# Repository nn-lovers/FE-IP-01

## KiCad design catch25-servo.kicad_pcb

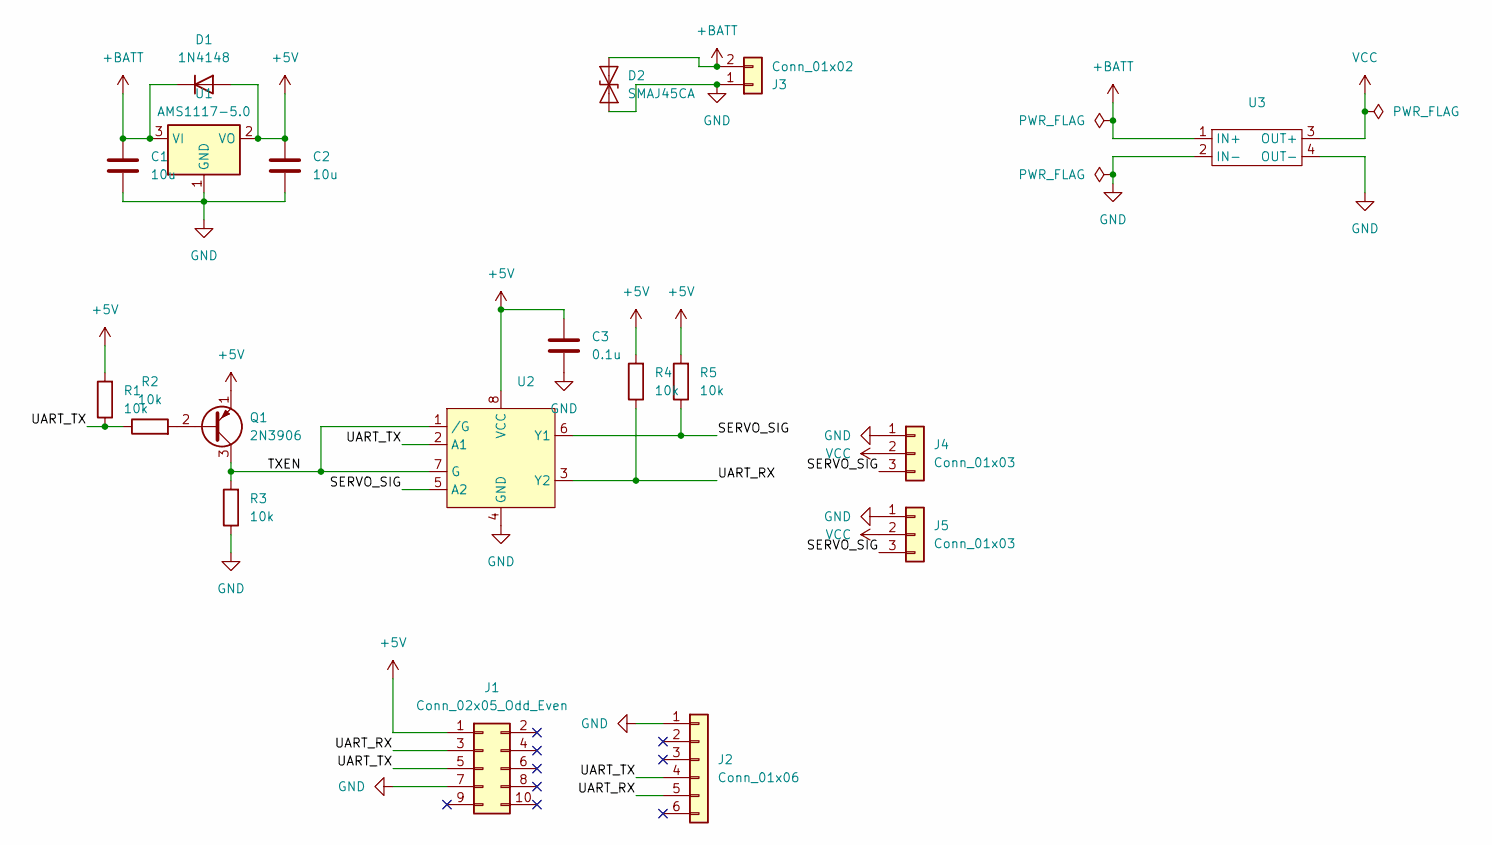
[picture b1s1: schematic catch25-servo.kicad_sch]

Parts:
C1, C2: 10u; C_0603_1608Metric_Pad1.08x0.95mm_HandSolder
C3: 0.1u; C_0603_1608Metric_Pad1.08x0.95mm_HandSolder
D1: 1N4148; D_DO-35_SOD27_P7.62mm_Horizontal
D2: SMAJ45CA; D_SMA_Handsoldering
J1: Conn_02x05_Odd_Even; PinSocket_2x05_P2.54mm_Horizontal
J2: Conn_01x06; PinSocket_1x06_P2.54mm_Vertical
J3: Conn_01x02; AMASS_XT30PW-M_1x02_P2.50mm_Horizontal
J4, J5: Conn_01x03; Molex_SPOX_5268-03A_1x03_P2.50mm_Horizontal
Q1: 2N3906; SuperSOT-3
R1, R2, R3, R4, R5: 10k; R_0603_1608Metric_Pad0.98x0.95mm_HandSolder
U1: AMS1117-5.0; SOT-223-3_TabPin2
U2: VSSOP-8_2.3x2mm_P0.5mm
U3: OKL

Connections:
+5V: C2.1, C3.1, D1.2 (A), J1.1, Q1.1 (E), R1.2, R4.2, R5.2, U1.2 (VO), U2.8 (VCC)
+BATT: C1.1, D1.1 (K), D2.2 (A2), J3.2, U1.3 (VI), U3.1 (IN+)
/SERVO_SIG: J4.3, J5.3, R5.1, U2.5 (A2), U2.6 (Y1)
/TXEN: Q1.3 (C), R3.2, U2.1 (/G), U2.7 (G)
/UART_RX: J1.3, J2.5, R4.1, U2.3 (Y2)
/UART_TX: J1.5, J2.4, R1.1, R2.1, U2.2 (A1)
GND: C1.2, C2.2, C3.2, D2.1 (A1), J1.7, J2.1, J3.1, J4.1, J5.1, R3.1, U1.1 (GND), U2.4 (GND), U3.2 (IN-), U3.4 (OUT-)
unnamed: Q1.2 (B), R2.2
VCC: J4.2, J5.2, U3.3 (OUT+)

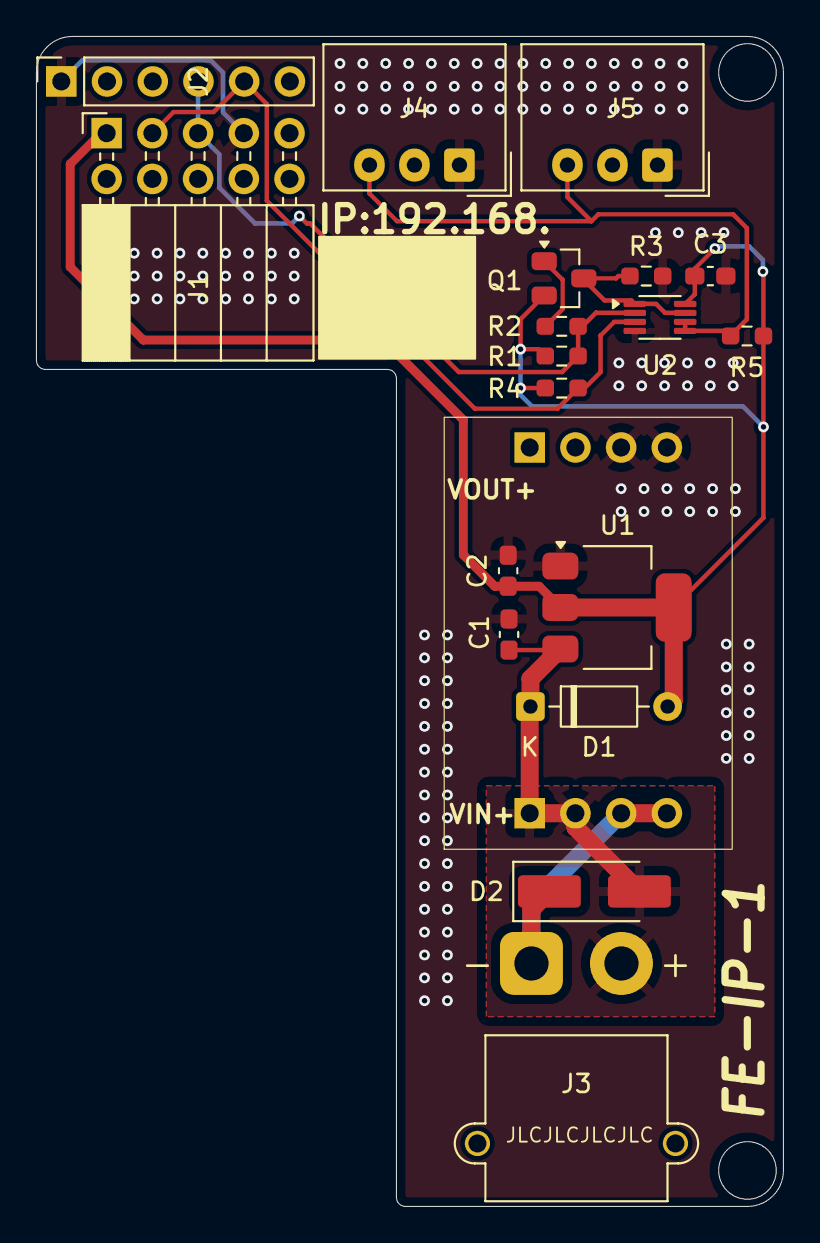
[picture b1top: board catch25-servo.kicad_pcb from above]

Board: 2 copper layers, 41.5 x 65.0 mm, 19 parts (0 on the bottom side), 9 nets.

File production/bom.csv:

Designator,Footprint,Quantity,Value,LCSC Part #
"C1, C2",0603,2,10u,
C3,0603,1,0.1u,
D1,D_DO-35_SOD27_P7.62mm_Horizontal,1,1N4148,
D2,D_SMA_Handsoldering,1,SMAJ45CA,
J1,PinSocket_2x05_P2.54mm_Horizontal,1,Conn_02x05_Odd_Even,
J2,PinSocket_1x06_P2.54mm_Vertical,1,Conn_01x06,
J3,AMASS_XT30PW-M_1x02_P2.50mm_Horizontal,1,Conn_01x02,
"J4, J5",Molex_SPOX_5268-03A_1x03_P2.50mm_Horizontal,2,Conn_01x03,
Q1,SuperSOT-3,1,2N3906,
"R1, R2, R3, R4, R5",0603,5,10k,
U1,SOT-223-3_TabPin2,1,AMS1117-5.0,
U2,VSSOP-8_2.3x2mm_P0.5mm,1,~,
U3,OKL,1,~,OKL-T/6-W12N-C

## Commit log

2025-06-01 update files
2025-06-01 add files
2025-06-03 update resources
2025-07-17 changed okl to breakout board
